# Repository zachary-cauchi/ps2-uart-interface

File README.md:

# ps2-uart-interface

Schematics for accessing the PS2 serial interface. This is based on the [ps2 serial cable mod](https://ps2-home.com/forum/viewtopic.php?t=4828).

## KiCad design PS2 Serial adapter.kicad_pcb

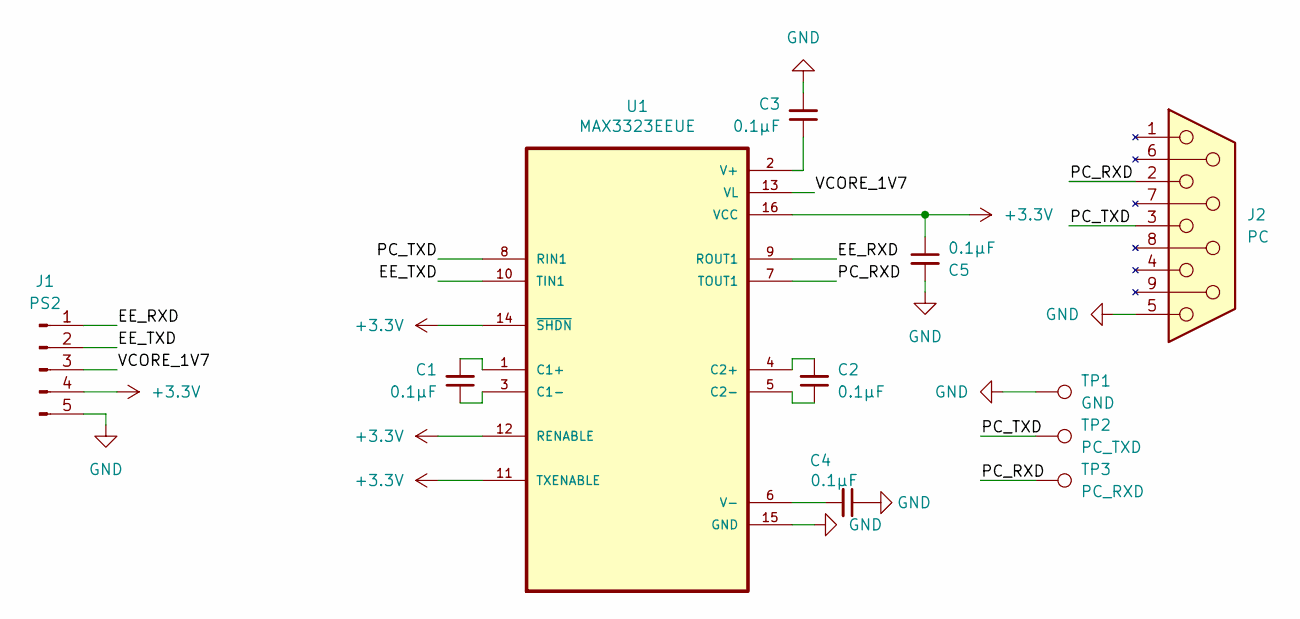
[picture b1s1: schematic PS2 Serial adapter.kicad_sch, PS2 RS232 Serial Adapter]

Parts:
C1, C2, C3, C4, C5: 0.1μF; C_0805_2012Metric_Pad1.18x1.45mm_HandSolder
J1: PS2; JST_XH_S5B-XH-A_1x05_P2.50mm_Horizontal
J2: PC; DSUB-9_Socket_EdgeMount_P2.77mm
TP1: GND; TestPoint_Pad_2.0x2.0mm
TP2: PC_TXD; TestPoint_Pad_2.0x2.0mm
TP3: PC_RXD; TestPoint_Pad_2.0x2.0mm
U1: MAX3323EEUE; SOP65P640X110-16N; DigiKey_Part_Number MAX3323EEUE+-ND

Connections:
+3.3V: C5.1, J1.4 (VCC_3V3), U1.11 (TXENABLE), U1.12 (RENABLE), U1.14 (~SHDN), U1.16 (VCC)
/EE_RXD: J1.1 (EE_RXD), U1.9 (ROUT1)
/EE_TXD: J1.2 (EE_TXD), U1.10 (TIN1)
/PC_RXD: J2.2, TP3.1, U1.7 (TOUT1)
/PC_TXD: J2.3, TP2.1, U1.8 (RIN1)
/VCORE_1V7: J1.3 (VCORE_1V7), U1.13 (VL)
GND: C3.2, C4.1, C5.2, J1.5 (GND), J2.5, TP1.1, U1.15 (GND)
unnamed: C1.2, U1.1 (C1+)
unnamed: C1.1, U1.3 (C1-)
unnamed: C2.2, U1.4 (C2+)
unnamed: C2.1, U1.5 (C2-)
unnamed: C3.1, U1.2 (V+)
unnamed: C4.2, U1.6 (V-)

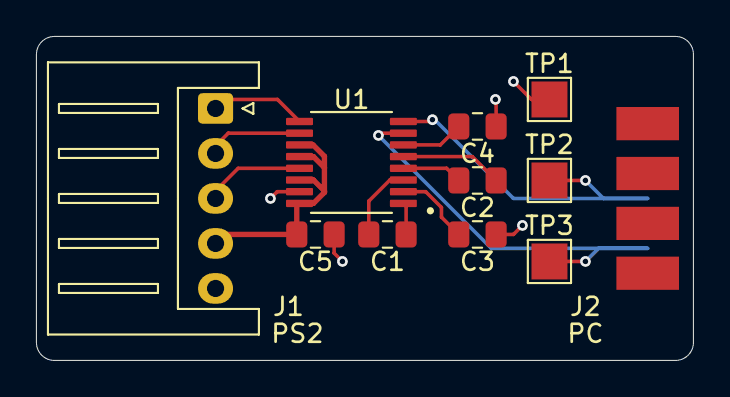
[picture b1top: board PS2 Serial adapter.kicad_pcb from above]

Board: 2 copper layers, 36.5 x 18.0 mm, 11 parts (1 on the bottom side), 13 nets.

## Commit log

2025-03-31 Add base PCB schem and layout
2025-03-31 Update footprints, 3V3 width and begin bom
2025-03-31 Add last LCSC parts
2025-03-31 Fillet corners, add missing labels, fix trace
2025-03-31 Add production dir to ignore
